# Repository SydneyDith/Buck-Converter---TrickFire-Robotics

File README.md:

# Buck Converter - Power Distribution (12V-24V @3A) - TrickFire Robotics 
Independently developed a 24V-12V buck converter using the TPS563300 IC designed to operate at 3A for use in TrickFire Robotics power distribution system. Performed calculations to find ideal component values for best performance while referring to the IC datasheet. Designed schematics and PCBs on KiCAD iterating and refining prototypes as I learned from previous mistakes.

| Parameter | Value |
| :--- | :--- |
| **Input Voltage** | 24V |
| **Output Voltage** | 12V |
| **Max Current** | 3A |

## Schematic And PCB Design

To develop the buck converter schematic I frequently referred to the main operating IC's datasheet: [datasheet](https://www.ti.com/lit/ds/symlink/tps563300.pdf)

It provides formulas and specifications of the buck IC I used to develop this schematic. When selecting footprints for my components, I opted for the 0603 package when possible. For the resistors and capacitors, selecting the handsolder footprint made handsoldering my PCB much easier later on. In my first iteration of schematic design, I made the mistake of choosing an inductor footprint that was only rated for a current of ~250mA. When double checking my work, however, I found this mistake and quickly sought another component that could support my desired specifications of 3A. Luckily this fix was easy at this stage in the project, but if left overlooked, my final design wouldn't have worked as intended and cost the project time and money to fix. I quickly found a replacement and ensured my other components were rated for this current and voltage.

Based on the [datasheet](https://www.ti.com/lit/ds/symlink/tps563300.pdf), the following layout/placement strategies were employed:

*  Placed IC, inductor, and caps on the same side of the board.
*  Positioned input/output caps as close to the IC as possible.
*  Placed 0.1µF decoupling caps directly next to the power pins.
*  Kept the switching trace small and current loop small to minimize noise.
*  Positioned the FB divider near the pin and away from noisy power traces.

In my initial design, I emphasized the placement strategies listed above but once again failed to account for the 3A of current flowing through the buck. I used the default trace size of 0.2mm for my 24V input line when I should've used around 1.2mm to support the current. With the 0.2mm trace, my buck could only provide less than an amp of current. I stumbled upon this issue when doing research about PCB design and learned that when dealing with power distribution systems, trace width and trace size really matters. Initially, this wasn't something that I emphasized enough. Below is my revised pcb where I increased the trace size, adjusted placements, and created a ground plane:

The followng image shows the 3D render of the PCB design above:

| **PCB Layout 3D Render** |
| :---: |
|  |

<br>

## Results
| **Soldered Buck** |
| :---: |
|  |

When soldering the pcb, I found the greatest challenge was handsoldering the TPS563300 IC. It was about the size of two grains of rice side by side, and it was an 8 pin IC. However, with patience and some flux, I was able to solder the IC, esuring no shorts between legs. When soldering the big inductor, I found success in swapping my soldering iron's tip to a large chisel that transfered heat easily. The 0603 package parts were pretty straight forward. Using a fine gauge leaded solder made soldering these components easy.

| **Output of Buck Converter (24V Input)** |
| :---: |
|  |

Finally I was able to test my 24V-12V buck converter. As to not immediately damage the buck converter, I used a lab bench multimeter which has a very large internal resistance. When measuring the output voltage, I could ensure there would be a very small amount of current and could specifically measure the output voltage without the risk of damaging anything. I found 12.9V at the output, which seemed to be a good sign. This error could very well be attributed to component tolerances, inaccuracy in the IC, or filtering issues. If I desired a cleaner output, I would switch to more (expensive) tolerant resistors and improve input and output filtering.

<br>

## Conclusion

My previous experience in pcb design had been in communication systems using the ATmega328p microcontroller and several sensors through I2C communication in my Heartrate Monitor Smartwatch. However, this project introduced me to basic power electronics and pcb deign strategies to employ when dealing with higher voltages and currents. In communication, I was dealing with digital electronics and the goal was signal integrity to ensure data reached the sensors. In power electronics, however, traces will burn if they aren't wide enough for the current, components must be strictly rated for the voltage and current, and component placements can have a large impact on the electromagnetic interference. 

This project has served as a great introduction to one of the many subfields of Electrical Engineering where I have been able to apply and expand upon class concepts. I can't wait to dive deeper into the world of power electronics for future projects.

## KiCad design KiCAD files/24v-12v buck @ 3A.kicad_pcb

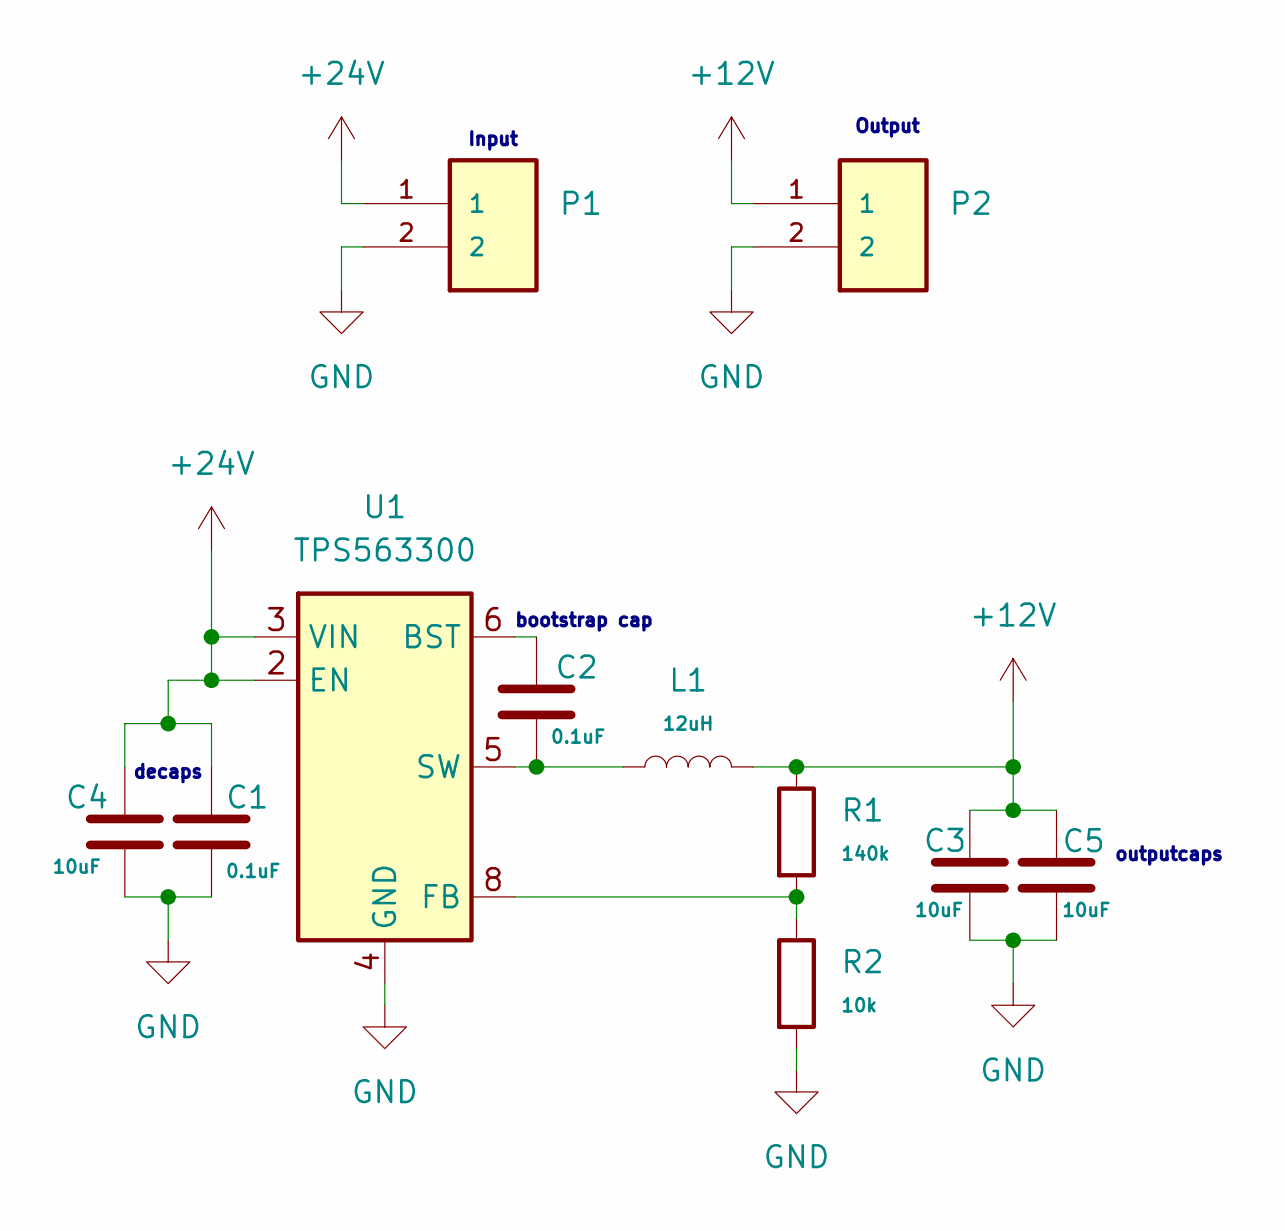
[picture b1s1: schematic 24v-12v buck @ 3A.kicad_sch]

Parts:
C1, C2: 0.1uF; C_0603_1608Metric_Pad1.08x0.95mm_HandSolder
C3, C4, C5: 10uF; C_0603_1608Metric_Pad1.08x0.95mm_HandSolder
L1: 12uH; L_Bourns_SRR1208_12.7x12.7mm
P1, P2: 282837-2; TE_282837-2; PARTREV G3
R1: 140k; R_0603_1608Metric_Pad0.98x0.95mm_HandSolder
R2: 10k; R_0603_1608Metric_Pad0.98x0.95mm_HandSolder
U1: TPS563300; SOT-583-8

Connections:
+12V: C3.1, C5.1, L1.2, P2.1, R1.1
+24V: C1.1, C4.1, P1.1, U1.2 (EN), U1.3 (VIN)
GND: C1.2, C3.2, C4.2, C5.2, P1.2, P2.2, R2.2, U1.4 (GND)
unnamed: C2.1, U1.6 (BST)
unnamed: R1.2, R2.1, U1.8 (FB)
unnamed: C2.2, L1.1, U1.5 (SW)

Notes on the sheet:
decaps
bootstrap cap
Output
Input
outputcaps

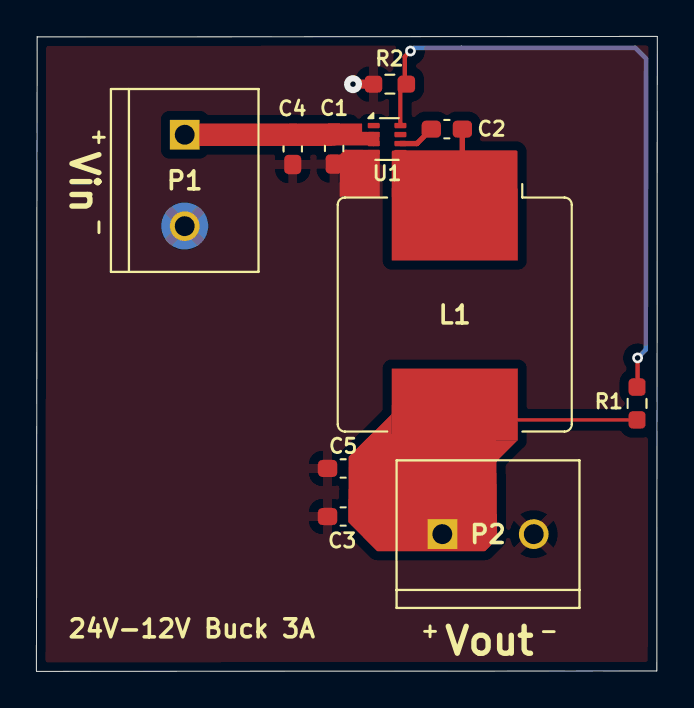
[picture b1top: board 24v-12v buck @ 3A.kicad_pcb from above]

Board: 2 copper layers, 34.5 x 35.3 mm, 11 parts (0 on the bottom side), 6 nets.

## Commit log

2026-04-05 Add image reference for buck converter schematic
    Added an image reference for the buck converter schematic.
2026-04-05 Rename buckconverterpcb.PNG to pcb.PNG
2026-04-05 Rename buckconverterschem.PNG to schem.PNG
2026-04-05 Rename buckconverterpcbrender.PNG to pcbrender.PNG
2026-04-05 Update README with schematic design details
    Corrected grammar and added a reference to the IC datasheet.
2026-04-06 Rename buckconverterpcbv1.PNG to pcbv1.PNG
2026-04-06 Rename pcb.PNG to buckconverterpcb.PNG
2026-04-06 Rename pcbrender.PNG to buckconverterpcbrender.PNG
2026-04-06 Revise README for clarity and additional visuals
    Updated README to improve project title and section headings. Added details about PCB design revisions and included additional visuals.
2026-04-06 Rename IMG_5143.JPG to buck1.JPG
2026-04-06 Rename IMG_5142.JPG to buck2.JPG
2026-04-06 Rename IMG_5103.JPG to bucktest.JPG
2026-04-06 Fix typos and enhance clarity in README.md
    Corrected typos and improved clarity in the README content, including references to the IC datasheet and PCB design considerations.
2026-04-08 Create KiCAD files
